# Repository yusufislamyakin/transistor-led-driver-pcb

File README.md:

# Transistor LED Driver PCB

## Overview
This project is a simple transistor-based LED driver circuit designed using KiCad.

## Working Principle
When the button is pressed, current flows into the transistor base.
The transistor turns on and allows current to flow through the LED.

## Components
- BC237 Transistor
- LED
- 330Ω resistor
- 10kΩ resistor
- Push button

## Images

### Schematic

### PCB Layout

### 3D View

## Tools Used
- KiCad
- KiCad PCB Editor
- KiCad 3D Viewer

## Project Files

You can find the complete KiCad project files in the `kicad` folder, including schematic and PCB layout.

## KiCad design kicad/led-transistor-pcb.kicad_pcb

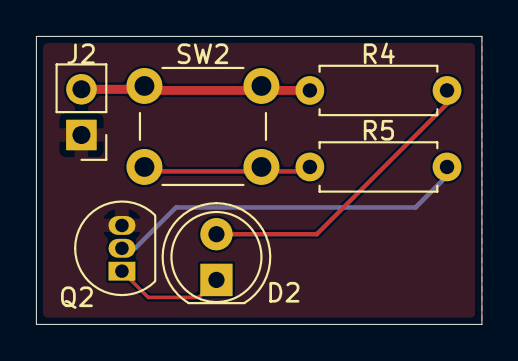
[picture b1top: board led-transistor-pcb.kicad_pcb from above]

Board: 2 copper layers, 24.8 x 16.0 mm, 6 parts (0 on the bottom side), 6 nets.

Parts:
D2: LED; LED_D5.0mm
J2: Conn_01x02_Socket; PinHeader_1x02_P2.54mm_Vertical
Q2: BC237; TO-92_Inline
R4: 330; R_Axial_DIN0207_L6.3mm_D2.5mm_P7.62mm_Horizontal
R5: 10k; R_Axial_DIN0207_L6.3mm_D2.5mm_P7.62mm_Horizontal
SW2: SW_Push; SW_PUSH_6mm

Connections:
+5V: J2.2, R4.1, SW2.1
GND: J2.1, Q2.3 (E)
unnamed: D2.2 (A), R4.2
unnamed: D2.1 (K), Q2.1 (C)
unnamed: Q2.2 (B), R5.1
unnamed: R5.2, SW2.2

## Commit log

2026-05-01 Create README.md
    Add README file for PCB project
